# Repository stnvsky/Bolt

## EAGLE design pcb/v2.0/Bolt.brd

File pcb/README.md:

## PCB layout errata

### Integrated flash pins

GPIO pins from 6 to 11 are connected to the integrated SPI flash memory and are not safe to use. PCB versions 1.x suffer from the lack of prior knowledge of that, what caused the ESP32 to not be able to boot after the motors with hall sensors have been connected to the board. To avoid building second version of the PCB (what would cost lots of time and money, especially with the current lack of the electronic parts on the market), I've decided to resign from distance sensors to gain additional pins to be used for the hall sensors. Frankly, there weren't any possibility to use distance sensors in the first place, since ESP32 doesn't have enough pins to support three not-really-necessary sensors without GPIO's expander. 

Pins IMU_CLK and IMU_CS are connected consequentially to the pins SHD (hold) and SWP (write protect). As those pins are not directly responsible for carrying information in the flash SPI bus and are connected to the IMU input pins (so they are sending information to IMU, not receiving), the impact can be possibly not disastrous. I leaved those pins as they are, since it would be very difficult to workaround the direct connection with the IMU chip.

Other pins used for the communication with the integrated flash are prepared to be connected with the hall sensors. Since the hall sensors are sending information and the same pins are connected to the MISO, MOSI, CLK ans CS pins in integrated flash, the hall sensors interfere with the flash memory and can cause the ESP32 to brick and cannot boot no more. That's why the hall sensors will be connected to alternative pins:

| Signal   | Original pin | Alternative pin |
| -------- | ------------ | --------------- |
| HALL_1_A | 21 (GPIO 7)  | 4 (GPIO 36)     |
| HALL_2_A | 22 (GPIO 8)  | 7 (GPIO 35)     |
| HALL_1_B | 20 (GPIO 6)  | 10 (GPIO 25)    |
| HALL_2_B | 19 (GPIO 11) | 11 (GPIO 26)    |

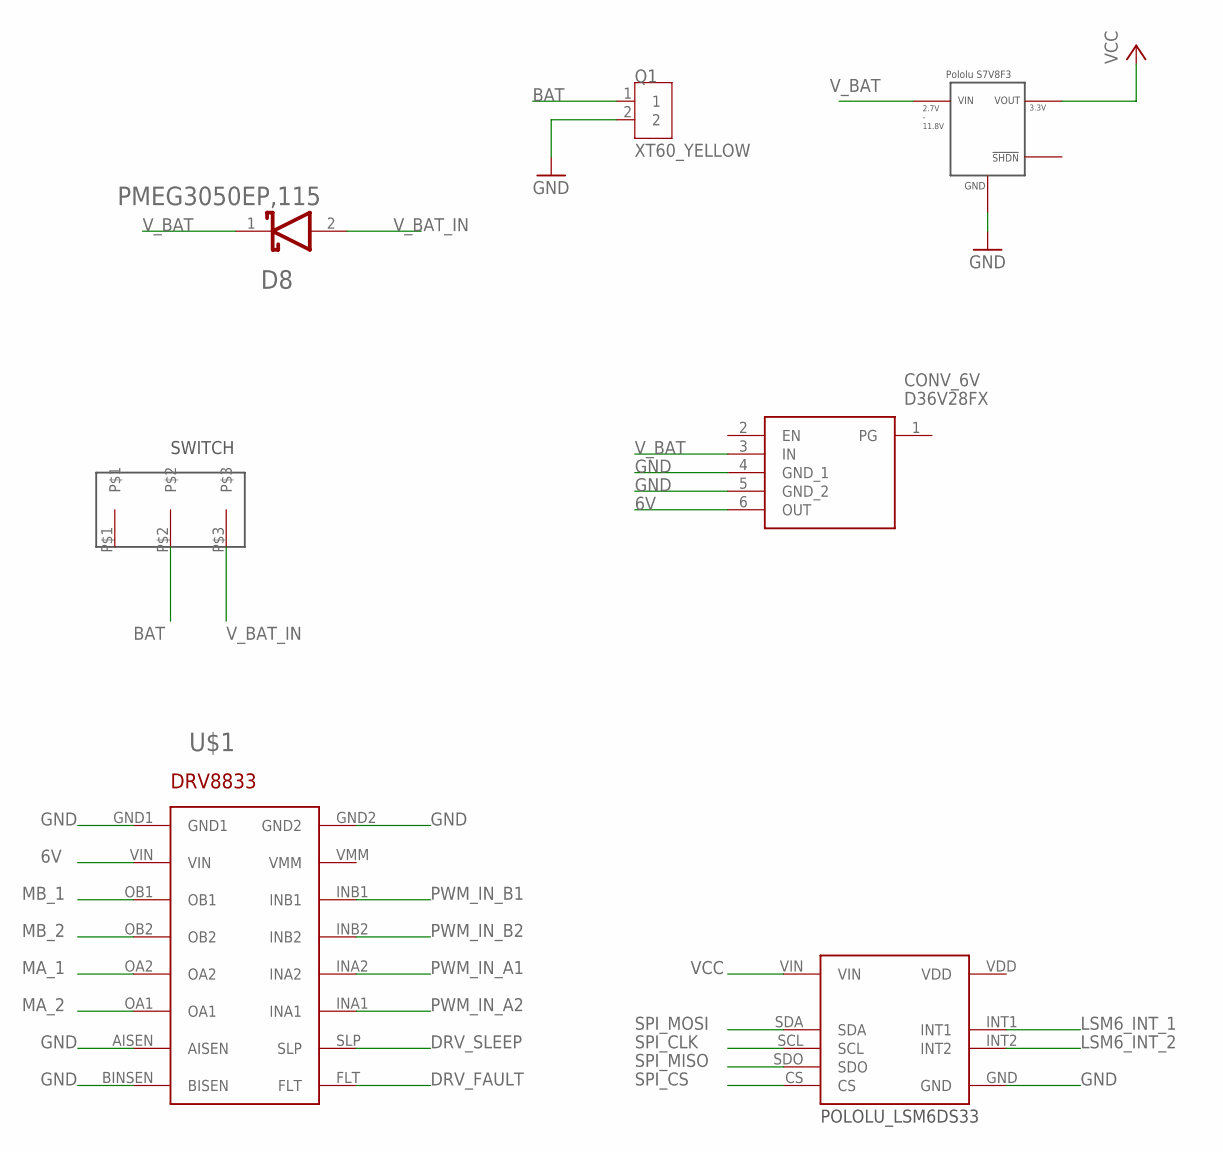
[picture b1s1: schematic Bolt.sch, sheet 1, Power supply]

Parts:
CONV_3V3: S7V8F3
CONV_6V: D36V28FX
D8: NEXPERIA_PMEG3050EP,115NEXPERIA_PMEG3050EP,115_0_0; NEXPERIA_PMEG3050EP,115_0
Q1: XT60_YELLOW; AMASS_XT60PB-M
U$1: POLOLU-DRV8833
U$2: POLOLU_LSM6DS33
U$3: SWITCH

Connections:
6V: CONV_6V.6 (OUT), U$1.VIN
BAT: Q1.1, U$3.P$2
DRV_FAULT: U$1.FLT; also elsewhere on the board
DRV_SLEEP: U$1.SLP; also elsewhere on the board
GND: CONV_3V3.GND, CONV_6V.4 (GND_1), CONV_6V.5 (GND_2), Q1.2, U$1.AISEN, U$1.BINSEN (BISEN), U$1.GND1, U$1.GND2, U$2.GND; also elsewhere on the board
LSM6_INT_1: U$2.INT1; also elsewhere on the board
LSM6_INT_2: U$2.INT2; also elsewhere on the board
MA_1: U$1.OA2; also elsewhere on the board
MA_2: U$1.OA1; also elsewhere on the board
MB_1: U$1.OB1; also elsewhere on the board
MB_2: U$1.OB2; also elsewhere on the board
PWM_IN_A1: U$1.INA2; also elsewhere on the board
PWM_IN_A2: U$1.INA1; also elsewhere on the board
PWM_IN_B1: U$1.INB1; also elsewhere on the board
PWM_IN_B2: U$1.INB2; also elsewhere on the board
SPI_CLK: U$2.SCL; also elsewhere on the board
SPI_CS: U$2.CS; also elsewhere on the board
SPI_MISO: U$2.SDO; also elsewhere on the board
SPI_MOSI: U$2.SDA; also elsewhere on the board
VCC: CONV_3V3.VOUT, U$2.VIN; also elsewhere on the board
V_BAT: CONV_3V3.VIN, CONV_6V.3 (IN), D8.1 (CATHODE)
V_BAT_IN: D8.2 (ANODE), U$3.P$3

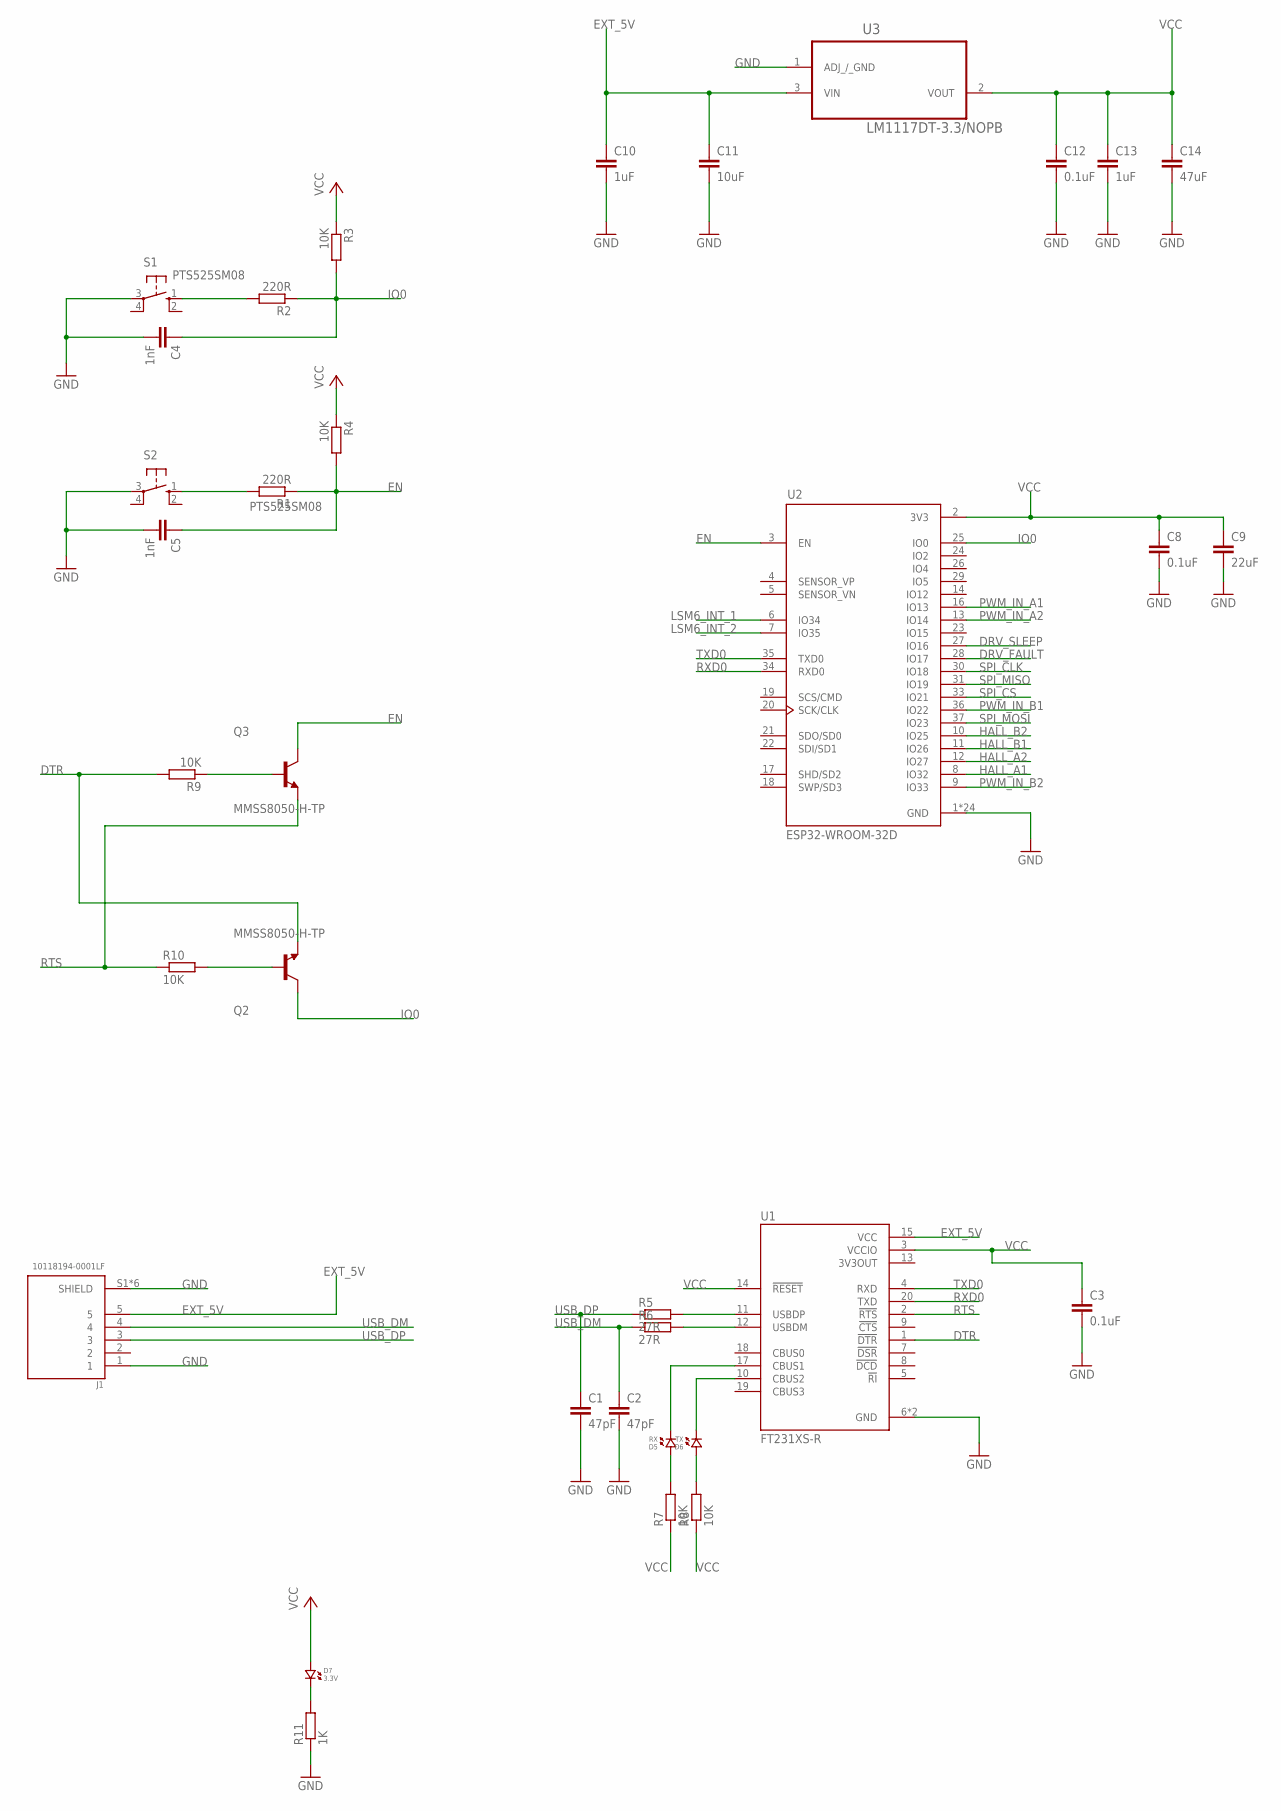
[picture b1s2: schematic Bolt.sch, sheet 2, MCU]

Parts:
C1, C2: 47pF; C0805K
C3, C8, C12: 0.1uF; C0805K
C4, C5: 1nF; C0805K
C9: 22uF; C0805K
C10, C13: 1uF; C0805K
C11: 10uF; C0805K
C14: 47uF; C0805K
D5: RX; 0805.LED
D6: TX; 0805.LED
D7: 3.3V; 0805.LED
J1: 10118194-0001LF; AMPHENOL_10118194-0001LF
Q2, Q3: MMSS8050-H-TP; TRANS_MMSS8050-H-TP
R1, R2: 220R; R0805
R3, R4, R7, R8, R9, R10: 10K; R0805
R5, R6: 27R; R0805
R11: 1K; R0805
S1, S2: PTS525SM08; SM08
U1: FT231XS-R; SOP63P599X175-20N
U2: ESP32-WROOM-32D; MODULE_ESP32-WROOM-32D
U3: LM1117DT-3.3/NOPB; TO228P970X238-3N

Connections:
3V3OUT: U1.13 (3V3OUT)
DRV_FAULT: U2.28 (IO17); also elsewhere on the board
DRV_SLEEP: U2.27 (IO16); also elsewhere on the board
DTR: Q2.2 (E), R9.2, U1.1 (!DTR)
EN: C5.1, Q3.3 (C), R1.1, R4.2, U2.3 (EN)
EXT_5V: C10.1, C11.1, J1.5, U1.15 (VCC), U3.3 (VIN)
GND: C1.2, C2.2, C3.2, C4.2, C5.2, C8.2, C9.2, C10.2, C11.2, C12.2, C13.2, C14.2, J1.1, J1.S1 (SHIELD), J1.S2 (SHIELD), J1.S3 (SHIELD), J1.S4 (SHIELD), J1.S5 (SHIELD), J1.S6 (SHIELD), R11.1, S1.3, S2.3, U1.6 (GND), U1.16 (GND), U2.1 (GND), U2.15 (GND), U2.38 (GND), U2.39_1 (GND), U2.39_2 (GND), U2.39_3 (GND), U2.39_4 (GND), U2.39_5 (GND), U2.39_6 (GND), U2.39_7 (GND), U2.39_8 (GND), U2.39_9 (GND), U2.39_10 (GND), U2.39_11 (GND), U2.39_12 (GND), U2.39_13 (GND), U2.39_14 (GND), U2.39_15 (GND), U2.39_16 (GND), U2.39_17 (GND), U2.39_18 (GND), U2.39_19 (GND), U2.39_20 (GND), U2.39_21 (GND), U3.1 (ADJ_/_GND); also elsewhere on the board
HALL_A1: U2.8 (IO32); also elsewhere on the board
HALL_A2: U2.12 (IO27); also elsewhere on the board
HALL_B1: U2.11 (IO26); also elsewhere on the board
HALL_B2: U2.10 (IO25); also elsewhere on the board
IO0: C4.1, Q2.3 (C), R2.1, R3.2, U2.25 (IO0)
LSM6_INT_1: U2.6 (IO34); also elsewhere on the board
LSM6_INT_2: U2.7 (IO35); also elsewhere on the board
unnamed: Q2.1 (B), R10.2
unnamed: D7.P$2 (2), R11.2
unnamed: D5.P$1 (1), R7.2
unnamed: R5.2, U1.11 (USBDP)
unnamed: R6.2, U1.12 (USBDM)
unnamed: R2.2, S1.1 (S)
unnamed: R1.2, S2.1 (S)
unnamed: Q3.1 (B), R9.1
unnamed: D5.P$2 (2), U1.17 (CBUS1)
unnamed: D6.P$2 (2), U1.10 (CBUS2)
unnamed: D6.P$1 (1), R8.2
PWM_IN_A1: U2.16 (IO13); also elsewhere on the board
PWM_IN_A2: U2.13 (IO14); also elsewhere on the board
PWM_IN_B1: U2.36 (IO22); also elsewhere on the board
PWM_IN_B2: U2.9 (IO33); also elsewhere on the board
RTS: Q3.2 (E), R10.1, U1.2 (!RTS)
RXD0: U1.20 (TXD), U2.34 (RXD0)
SPI_CLK: U2.30 (IO18); also elsewhere on the board
SPI_CS: U2.33 (IO21); also elsewhere on the board
SPI_MISO: U2.31 (IO19); also elsewhere on the board
SPI_MOSI: U2.37 (IO23); also elsewhere on the board
TXD0: U1.4 (RXD), U2.35 (TXD0)
USB_DM: C2.1, J1.4, R6.1
USB_DP: C1.1, J1.3, R5.1
VCC: C3.1, C8.1, C9.1, C12.1, C13.1, C14.1, D7.P$1 (1), R3.1, R4.1, R7.1, R8.1, U1.3 (VCCIO), U1.14 (!RESET), U2.2 (3V3), U3.2 (VOUT); also elsewhere on the board

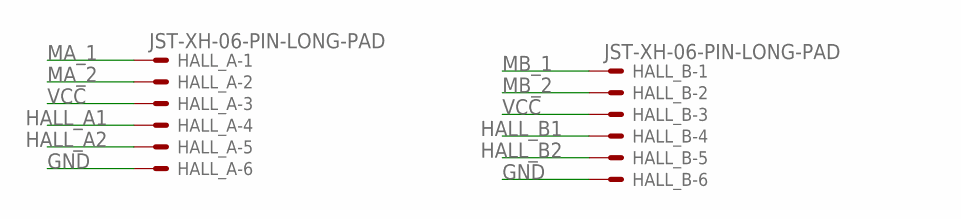
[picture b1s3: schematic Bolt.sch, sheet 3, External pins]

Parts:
HALL_A: JST-XH-06-PIN-LONG-PAD; JST-XH-06-PACKAGE-LONG-PAD
HALL_B: JST-XH-06-PIN-LONG-PAD; JST-XH-06-PACKAGE-LONG-PAD

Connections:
GND: HALL_A.6, HALL_B.6; also elsewhere on the board
HALL_A1: HALL_A.4; also elsewhere on the board
HALL_A2: HALL_A.5; also elsewhere on the board
HALL_B1: HALL_B.4; also elsewhere on the board
HALL_B2: HALL_B.5; also elsewhere on the board
MA_1: HALL_A.1; also elsewhere on the board
MA_2: HALL_A.2; also elsewhere on the board
MB_1: HALL_B.1; also elsewhere on the board
MB_2: HALL_B.2; also elsewhere on the board
VCC: HALL_A.3, HALL_B.3; also elsewhere on the board

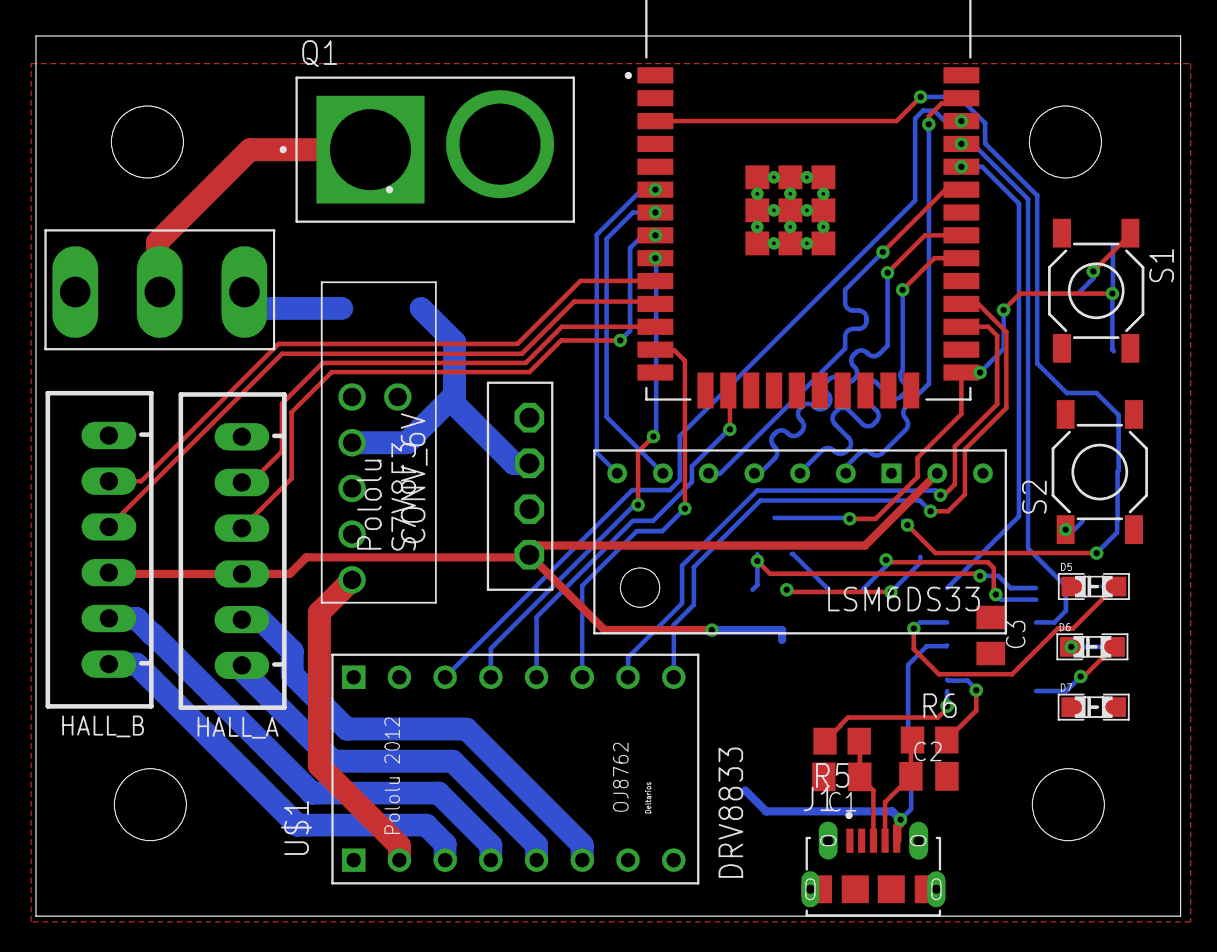
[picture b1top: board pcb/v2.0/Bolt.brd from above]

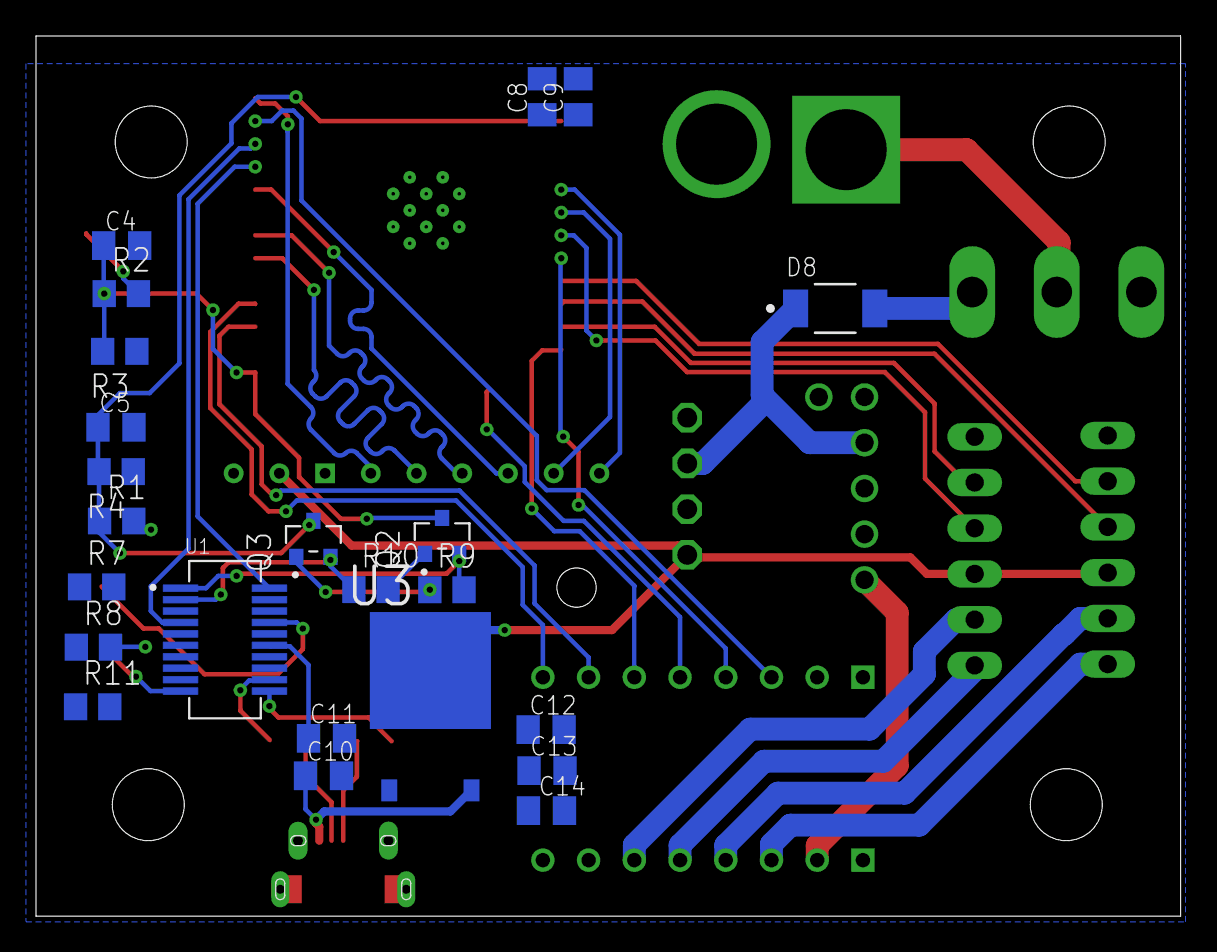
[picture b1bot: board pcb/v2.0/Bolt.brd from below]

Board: 2 copper layers, 63.6 x 48.9 mm, 43 parts (23 on the bottom side), 46 nets.

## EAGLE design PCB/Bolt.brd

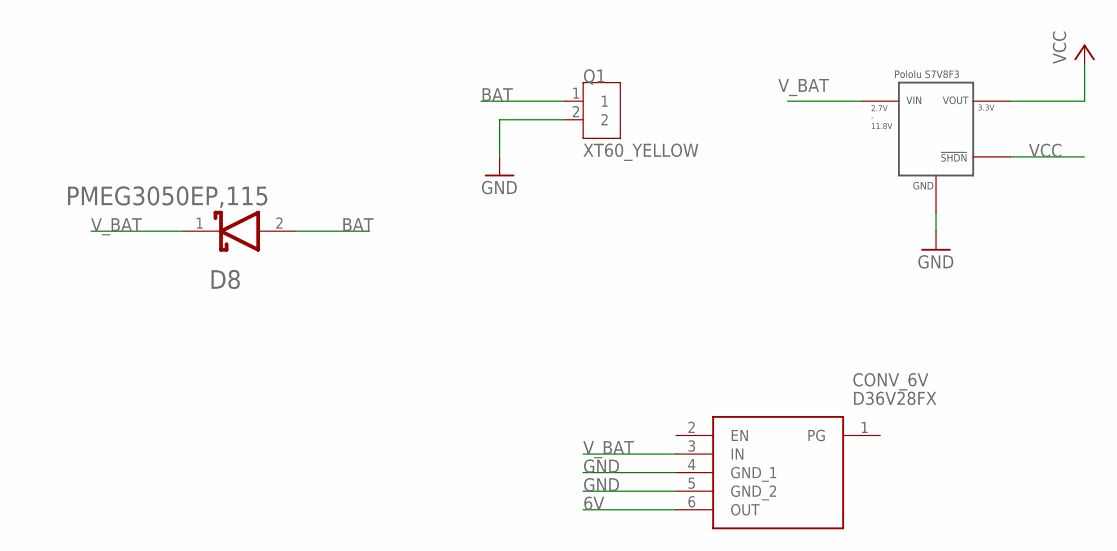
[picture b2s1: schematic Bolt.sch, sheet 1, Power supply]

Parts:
CONV_3V3: S7V8F3
CONV_6V: D36V28FX
D8: NEXPERIA_PMEG3050EP,115NEXPERIA_PMEG3050EP,115_0_0; NEXPERIA_PMEG3050EP,115_0
Q1: XT60_YELLOW; AMASS_XT60PB-M

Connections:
6V: CONV_6V.6 (OUT); also elsewhere on the board
BAT: D8.2 (ANODE), Q1.1
GND: CONV_3V3.GND, CONV_6V.4 (GND_1), CONV_6V.5 (GND_2), Q1.2; also elsewhere on the board
VCC: CONV_3V3.!SHDN, CONV_3V3.VOUT; also elsewhere on the board
V_BAT: CONV_3V3.VIN, CONV_6V.3 (IN), D8.1 (CATHODE)

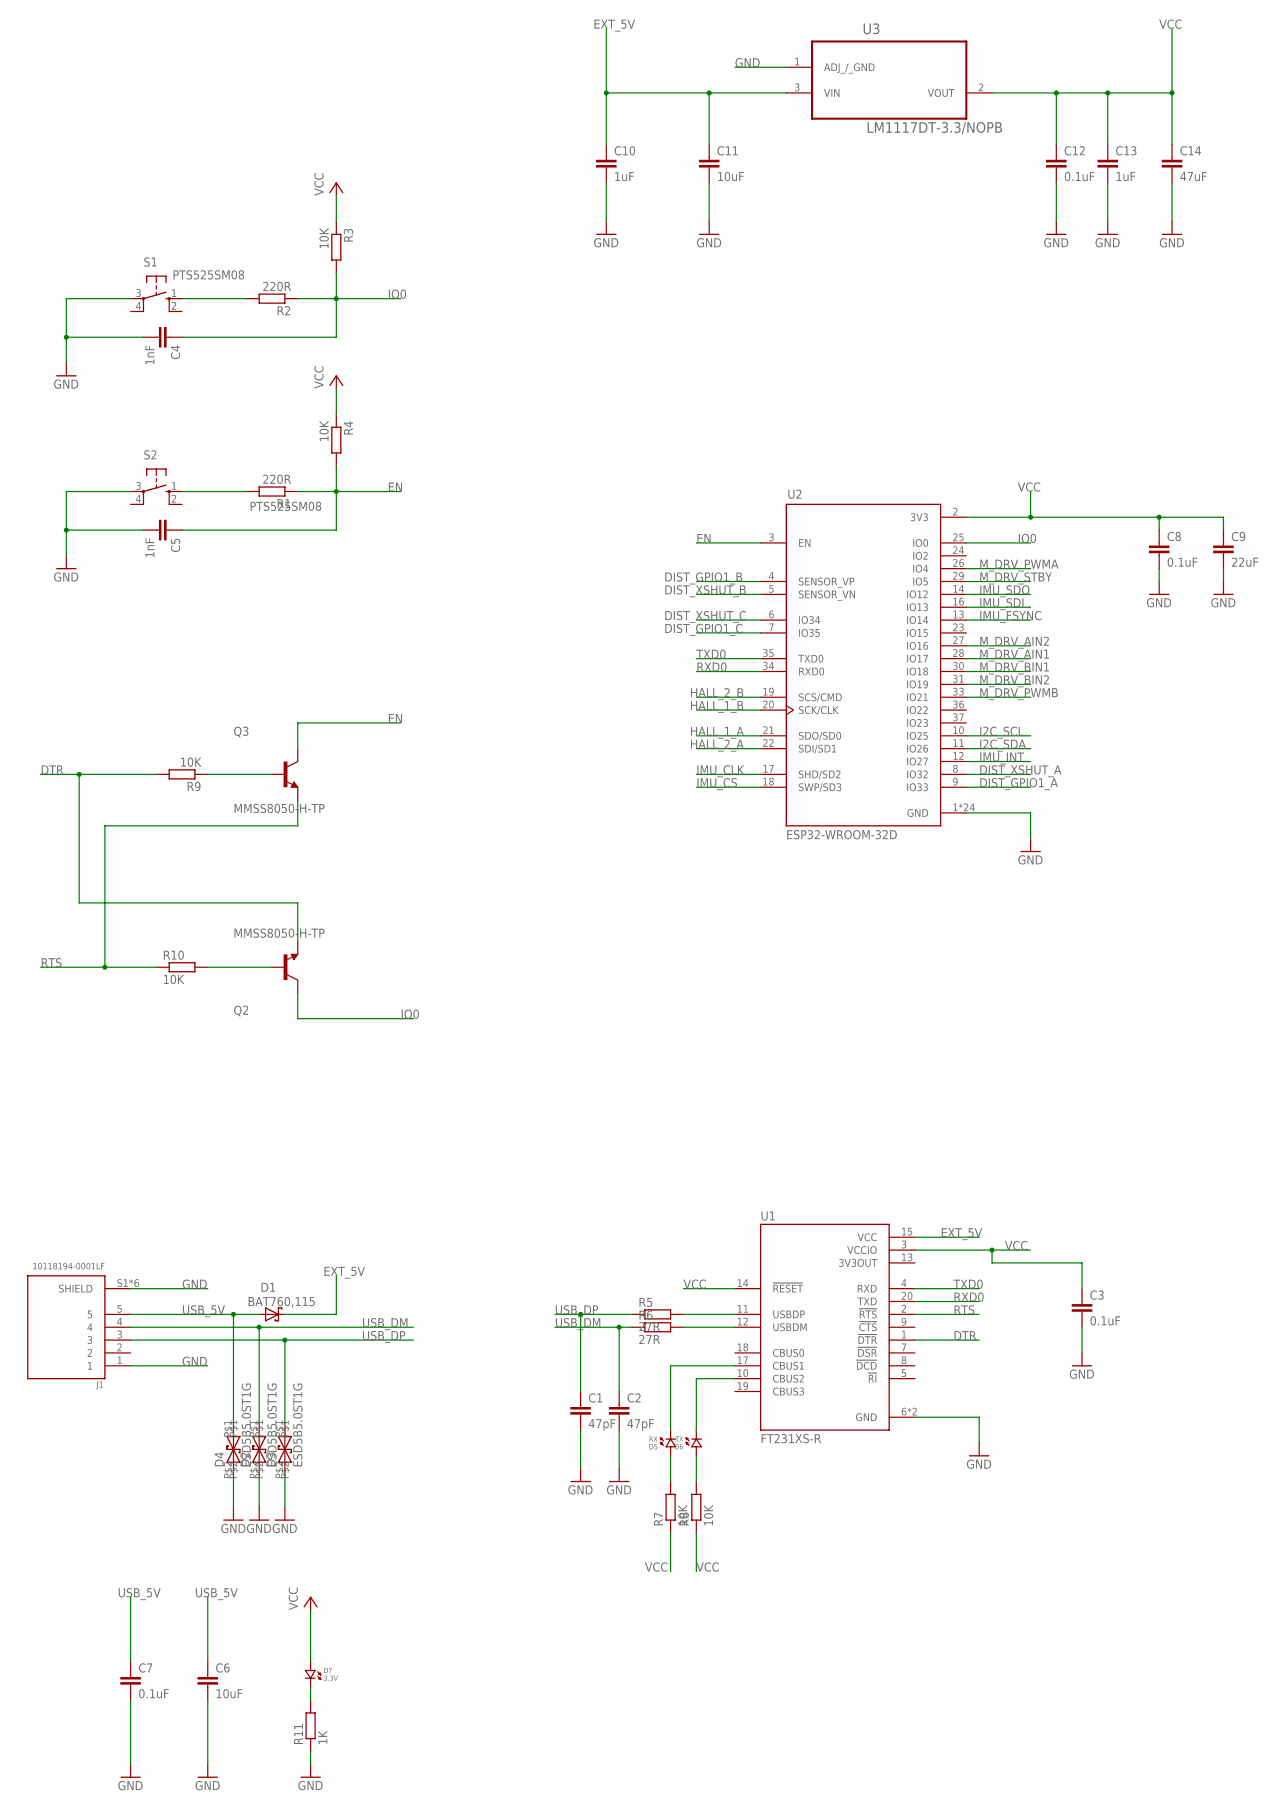
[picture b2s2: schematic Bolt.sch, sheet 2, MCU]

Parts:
C1, C2: 47pF; C0805K
C3, C7, C8, C12: 0.1uF; C0805K
C4, C5: 1nF; C0805K
C6, C11: 10uF; C0805K
C9: 22uF; C0805K
C10, C13: 1uF; C0805K
C14: 47uF; C0805K
D1: BAT760,115; SOD323(F)
D2, D3, D4: ESD5B5.0ST1G; SOD-523
D5: RX; 0805.LED
D6: TX; 0805.LED
D7: 3.3V; 0805.LED
J1: 10118194-0001LF; AMPHENOL_10118194-0001LF
Q2, Q3: MMSS8050-H-TP; TRANS_MMSS8050-H-TP
R1, R2: 220R; R0805
R3, R4, R7, R8, R9, R10: 10K; R0805
R5, R6: 27R; R0805
R11: 1K; R0805
S1, S2: PTS525SM08; SM08
U1: FT231XS-R; SOP63P599X175-20N
U2: ESP32-WROOM-32D; MODULE_ESP32-WROOM-32D
U3: LM1117DT-3.3/NOPB; TO228P970X238-3N

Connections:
3V3OUT: U1.13 (3V3OUT)
DIST_GPIO1_A: U2.9 (IO33); also elsewhere on the board
DIST_GPIO1_B: U2.4 (SENSOR_VP); also elsewhere on the board
DIST_GPIO1_C: U2.7 (IO35); also elsewhere on the board
DIST_XSHUT_A: U2.8 (IO32); also elsewhere on the board
DIST_XSHUT_B: U2.5 (SENSOR_VN); also elsewhere on the board
DIST_XSHUT_C: U2.6 (IO34); also elsewhere on the board
DTR: Q2.2 (E), R9.2, U1.1 (!DTR)
EN: C5.1, Q3.3 (C), R1.1, R4.2, U2.3 (EN)
EXT_5V: C10.1, C11.1, D1.1 (K), U1.15 (VCC), U3.3 (VIN)
GND: C1.2, C2.2, C3.2, C4.2, C5.2, C6.2, C7.2, C8.2, C9.2, C10.2, C11.2, C12.2, C13.2, C14.2, D2.P$2, D3.P$2, D4.P$2, J1.1, J1.S1 (SHIELD), J1.S2 (SHIELD), J1.S3 (SHIELD), J1.S4 (SHIELD), J1.S5 (SHIELD), J1.S6 (SHIELD), R11.1, S1.3, S2.3, U1.6 (GND), U1.16 (GND), U2.1 (GND), U2.15 (GND), U2.38 (GND), U2.39_1 (GND), U2.39_2 (GND), U2.39_3 (GND), U2.39_4 (GND), U2.39_5 (GND), U2.39_6 (GND), U2.39_7 (GND), U2.39_8 (GND), U2.39_9 (GND), U2.39_10 (GND), U2.39_11 (GND), U2.39_12 (GND), U2.39_13 (GND), U2.39_14 (GND), U2.39_15 (GND), U2.39_16 (GND), U2.39_17 (GND), U2.39_18 (GND), U2.39_19 (GND), U2.39_20 (GND), U2.39_21 (GND), U3.1 (ADJ_/_GND); also elsewhere on the board
HALL_1_A: U2.21 (SDO/SD0); also elsewhere on the board
HALL_1_B: U2.20 (SCK/CLK); also elsewhere on the board
HALL_2_A: U2.22 (SDI/SD1); also elsewhere on the board
HALL_2_B: U2.19 (SCS/CMD); also elsewhere on the board
I2C_SCL: U2.10 (IO25); also elsewhere on the board
I2C_SDA: U2.11 (IO26); also elsewhere on the board
IMU_CLK: U2.17 (SHD/SD2); also elsewhere on the board
IMU_CS: U2.18 (SWP/SD3); also elsewhere on the board
IMU_FSYNC: U2.13 (IO14); also elsewhere on the board
IMU_INT: U2.12 (IO27); also elsewhere on the board
IMU_SDI: U2.16 (IO13); also elsewhere on the board
IMU_SDO: U2.14 (IO12); also elsewhere on the board
IO0: C4.1, Q2.3 (C), R2.1, R3.2, U2.25 (IO0)
M_DRV_AIN1: U2.28 (IO17); also elsewhere on the board
M_DRV_AIN2: U2.27 (IO16); also elsewhere on the board
M_DRV_BIN1: U2.30 (IO18); also elsewhere on the board
M_DRV_BIN2: U2.31 (IO19); also elsewhere on the board
M_DRV_PWMA: U2.26 (IO4); also elsewhere on the board
M_DRV_PWMB: U2.33 (IO21); also elsewhere on the board
M_DRV_STBY: U2.29 (IO5); also elsewhere on the board
unnamed: Q2.1 (B), R10.2
unnamed: D7.P$2 (2), R11.2
unnamed: D5.P$1 (1), R7.2
unnamed: R5.2, U1.11 (USBDP)
unnamed: R6.2, U1.12 (USBDM)
unnamed: R2.2, S1.1 (S)
unnamed: R1.2, S2.1 (S)
unnamed: Q3.1 (B), R9.1
unnamed: D5.P$2 (2), U1.17 (CBUS1)
unnamed: D6.P$2 (2), U1.10 (CBUS2)
unnamed: D6.P$1 (1), R8.2
RTS: Q3.2 (E), R10.1, U1.2 (!RTS)
RXD0: U1.20 (TXD), U2.34 (RXD0)
TXD0: U1.4 (RXD), U2.35 (TXD0)
USB_5V: C6.1, C7.1, D1.2 (A), D4.P$1, J1.5
USB_DM: C2.1, D2.P$1, J1.4, R6.1
USB_DP: C1.1, D3.P$1, J1.3, R5.1
VCC: C3.1, C8.1, C9.1, C12.1, C13.1, C14.1, D7.P$1 (1), R3.1, R4.1, R7.1, R8.1, U1.3 (VCCIO), U1.14 (!RESET), U2.2 (3V3), U3.2 (VOUT); also elsewhere on the board

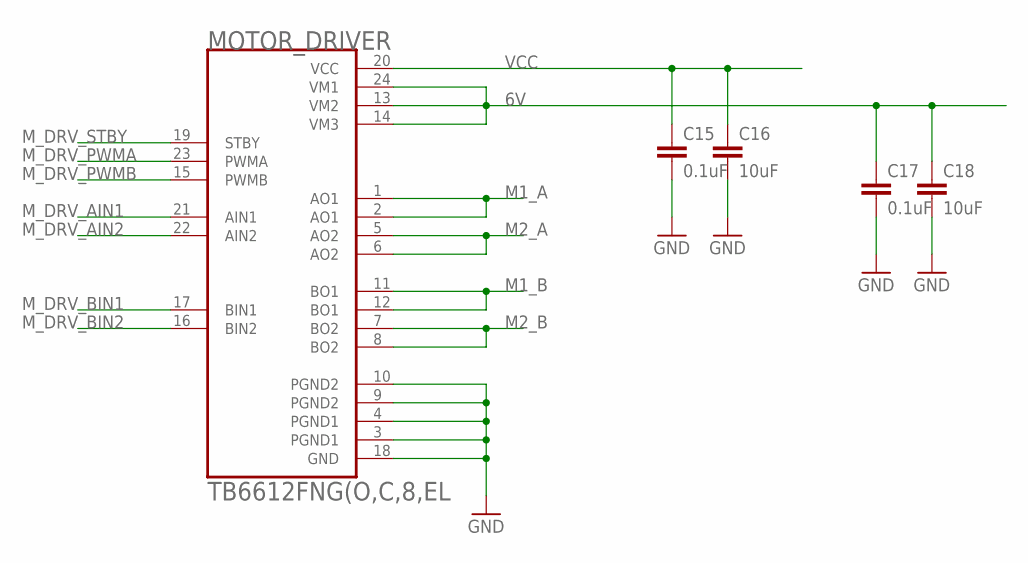
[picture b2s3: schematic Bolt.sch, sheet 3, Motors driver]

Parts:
C15, C17: 0.1uF; C0805K
C16, C18: 10uF; C0805K
MOTOR_DRIVER: TB6612FNG(O,C,8,EL; SOP65P760X160-24N

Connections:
6V: C17.1, C18.1, MOTOR_DRIVER.13 (VM2), MOTOR_DRIVER.14 (VM3), MOTOR_DRIVER.24 (VM1); also elsewhere on the board
GND: C15.2, C16.2, C17.2, C18.2, MOTOR_DRIVER.3 (PGND1), MOTOR_DRIVER.4 (PGND1), MOTOR_DRIVER.9 (PGND2), MOTOR_DRIVER.10 (PGND2), MOTOR_DRIVER.18 (GND); also elsewhere on the board
M1_A: MOTOR_DRIVER.1 (AO1), MOTOR_DRIVER.2 (AO1); also elsewhere on the board
M1_B: MOTOR_DRIVER.11 (BO1), MOTOR_DRIVER.12 (BO1); also elsewhere on the board
M2_A: MOTOR_DRIVER.5 (AO2), MOTOR_DRIVER.6 (AO2); also elsewhere on the board
M2_B: MOTOR_DRIVER.7 (BO2), MOTOR_DRIVER.8 (BO2); also elsewhere on the board
M_DRV_AIN1: MOTOR_DRIVER.21 (AIN1); also elsewhere on the board
M_DRV_AIN2: MOTOR_DRIVER.22 (AIN2); also elsewhere on the board
M_DRV_BIN1: MOTOR_DRIVER.17 (BIN1); also elsewhere on the board
M_DRV_BIN2: MOTOR_DRIVER.16 (BIN2); also elsewhere on the board
M_DRV_PWMA: MOTOR_DRIVER.23 (PWMA); also elsewhere on the board
M_DRV_PWMB: MOTOR_DRIVER.15 (PWMB); also elsewhere on the board
M_DRV_STBY: MOTOR_DRIVER.19 (STBY); also elsewhere on the board
VCC: C15.1, C16.1, MOTOR_DRIVER.20 (VCC); also elsewhere on the board

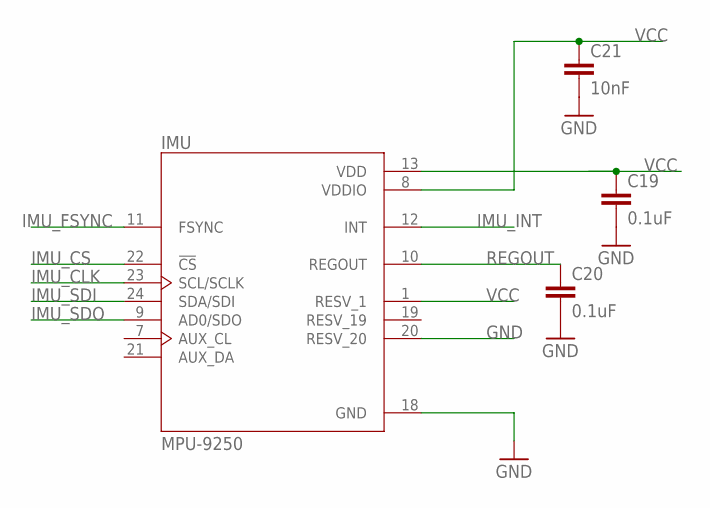
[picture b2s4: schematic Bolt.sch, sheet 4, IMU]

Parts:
C19, C20: 0.1uF; C0805K
C21: 10nF; C0805K
IMU: MPU-9250; QFN40P300X300X105-24N

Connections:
GND: C19.2, C20.2, C21.2, IMU.18 (GND), IMU.20 (RESV_20); also elsewhere on the board
IMU_CLK: IMU.23 (SCL/SCLK); also elsewhere on the board
IMU_CS: IMU.22 (!CS); also elsewhere on the board
IMU_FSYNC: IMU.11 (FSYNC); also elsewhere on the board
IMU_INT: IMU.12 (INT); also elsewhere on the board
IMU_SDI: IMU.24 (SDA/SDI); also elsewhere on the board
IMU_SDO: IMU.9 (AD0/SDO); also elsewhere on the board
REGOUT: C20.1, IMU.10 (REGOUT)
VCC: C19.1, C21.1, IMU.1 (RESV_1), IMU.8 (VDDIO), IMU.13 (VDD); also elsewhere on the board

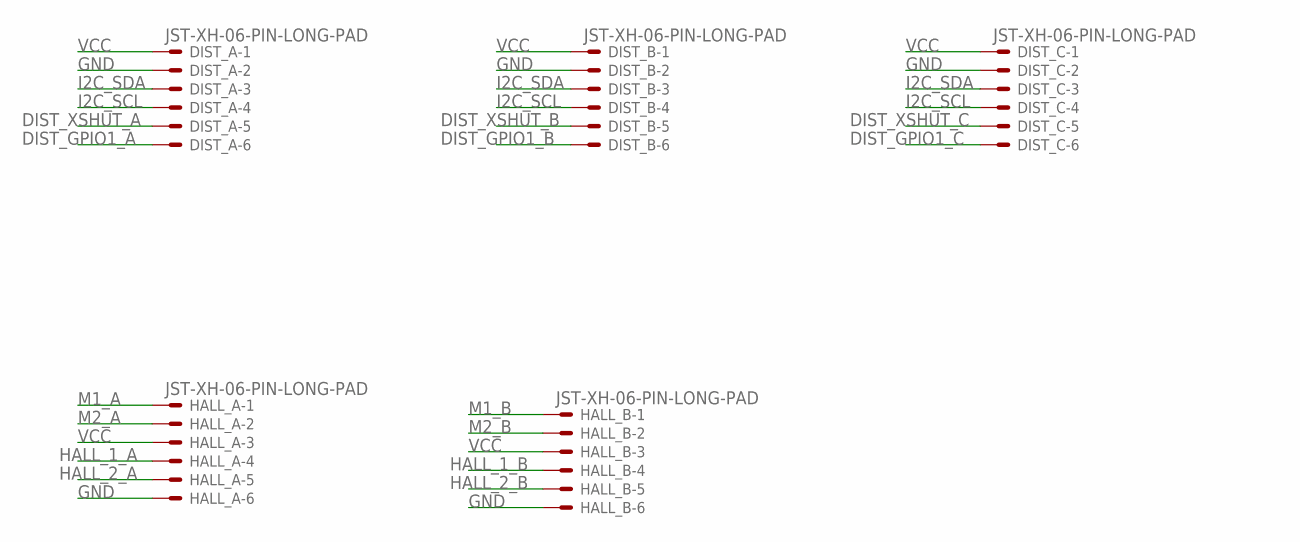
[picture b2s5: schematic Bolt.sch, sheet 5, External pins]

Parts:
DIST_A: JST-XH-06-PIN-LONG-PAD; JST-XH-06-PACKAGE-LONG-PAD
DIST_B: JST-XH-06-PIN-LONG-PAD; JST-XH-06-PACKAGE-LONG-PAD
DIST_C: JST-XH-06-PIN-LONG-PAD; JST-XH-06-PACKAGE-LONG-PAD
HALL_A: JST-XH-06-PIN-LONG-PAD; JST-XH-06-PACKAGE-LONG-PAD
HALL_B: JST-XH-06-PIN-LONG-PAD; JST-XH-06-PACKAGE-LONG-PAD

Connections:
DIST_GPIO1_A: DIST_A.6; also elsewhere on the board
DIST_GPIO1_B: DIST_B.6; also elsewhere on the board
DIST_GPIO1_C: DIST_C.6; also elsewhere on the board
DIST_XSHUT_A: DIST_A.5; also elsewhere on the board
DIST_XSHUT_B: DIST_B.5; also elsewhere on the board
DIST_XSHUT_C: DIST_C.5; also elsewhere on the board
GND: DIST_A.2, DIST_B.2, DIST_C.2, HALL_A.6, HALL_B.6; also elsewhere on the board
HALL_1_A: HALL_A.4; also elsewhere on the board
HALL_1_B: HALL_B.4; also elsewhere on the board
HALL_2_A: HALL_A.5; also elsewhere on the board
HALL_2_B: HALL_B.5; also elsewhere on the board
I2C_SCL: DIST_A.4, DIST_B.4, DIST_C.4; also elsewhere on the board
I2C_SDA: DIST_A.3, DIST_B.3, DIST_C.3; also elsewhere on the board
M1_A: HALL_A.1; also elsewhere on the board
M1_B: HALL_B.1; also elsewhere on the board
M2_A: HALL_A.2; also elsewhere on the board
M2_B: HALL_B.2; also elsewhere on the board
VCC: DIST_A.1, DIST_B.1, DIST_C.1, HALL_A.3, HALL_B.3; also elsewhere on the board

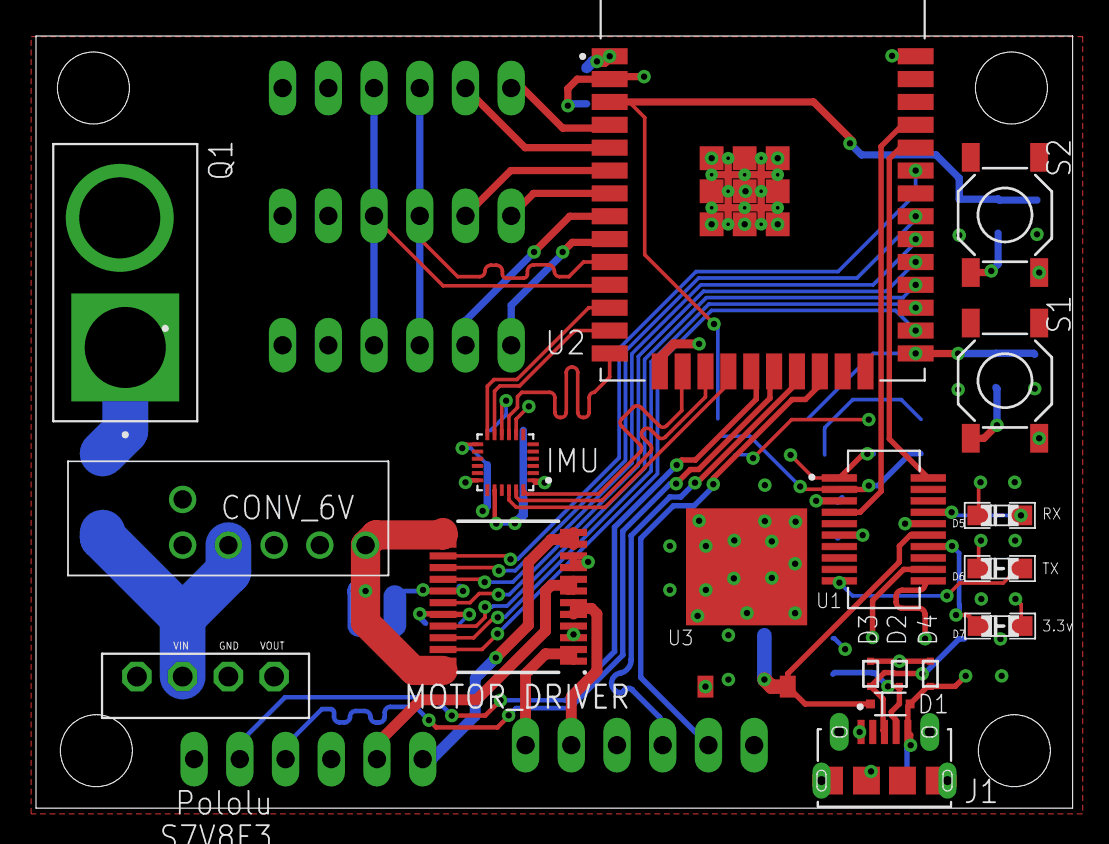
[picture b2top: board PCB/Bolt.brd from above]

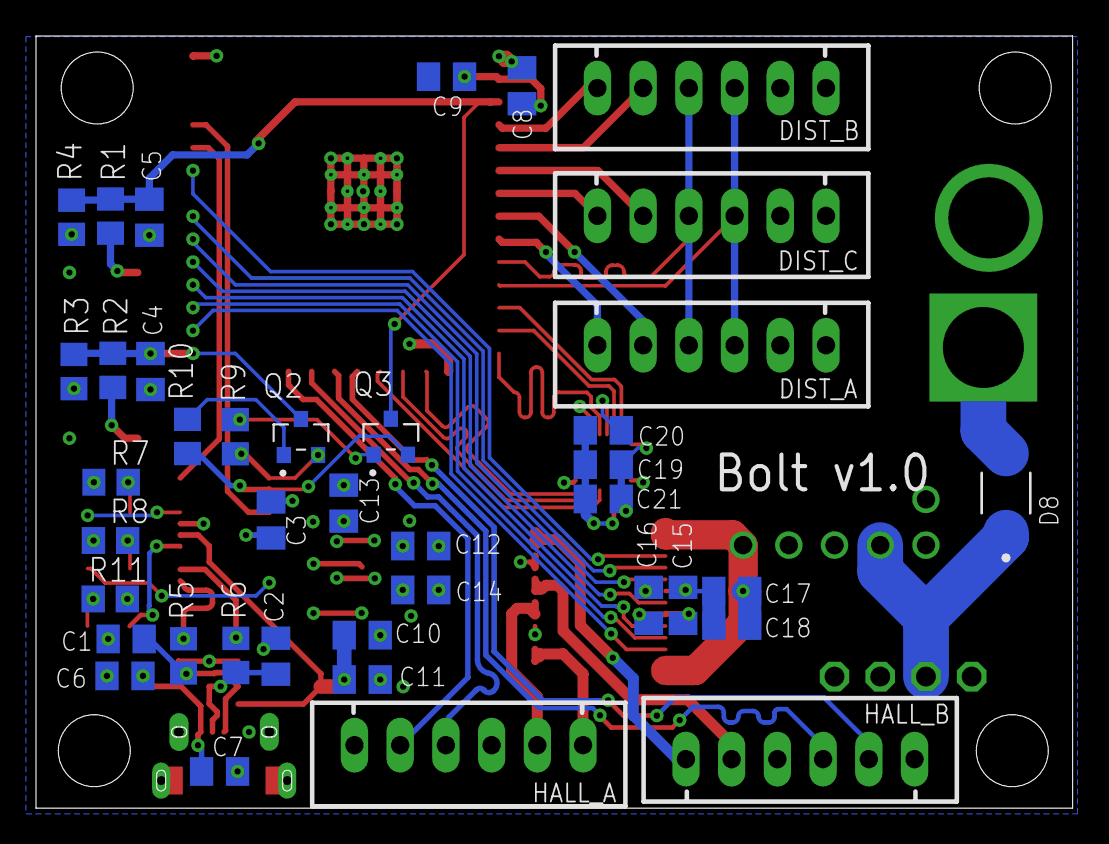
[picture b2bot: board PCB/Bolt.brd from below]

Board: 4 copper layers, 57.6 x 42.9 mm, 58 parts (40 on the bottom side), 56 nets.

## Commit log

2021-01-16 Choose of the pcb elements
2021-01-17 Added UART-USB converter
2021-01-18 Schematic completed
2021-01-19 Board - work in progress
2021-01-20 Board completed
2021-02-10 Bolt v1.0
2021-03-30 added initial code with some components, project refactoring
2021-04-18 Distance sensors - writing own library
2021-04-20 Distance sensors work
2021-04-26 refactor
2022-03-18 Fixed XSHUT routes on PCB resulting in Bolt v1.1
2022-06-07 Starting to work on the encoders
2022-06-08 Migrated to esp-idf v5.0, removed 'encoder' component
2022-06-09 Added first schetch for the vehicle model
2022-06-09 First prototype for the motors and dummy support for PCB
2022-06-09 Divided model to two bodies
2022-06-10 Fixed problems with the project, added fillets and holes in the motors base body
2022-06-10 Bottom part candidate
2022-06-10 Added PCB support model
2022-06-10 model candidate
2022-06-10 Vehicle structure model v1.0
2022-06-13 Added stl model of the whole vehicle construction
2022-06-14 Motors driver refactoring
2022-06-14 Working on the second version of the PCB
2022-06-15 Bolt v2.0 - before routing
2022-06-16 Routes except VCC
2022-06-17 Fixed removing v1.0 from the repository
2022-08-29 PCB v1.1 layout errata
2022-08-29 refactored directory pcb
2022-08-29 moved .gitignore to pcb subdirectories
2022-08-30 Refactoring, working example with acceleration
2022-08-30 pcb/v1.1./README.md update
2022-08-30 Implemented method for setting motors speed in range [-100, 100]
2022-08-30 Added example GPIO interrupt handlers
2022-09-02 Reading velocity and direction from hall sensors
2022-09-03 Get motors speed in [m/s]
2022-09-03 Updated the MPU library with DMP support
2022-09-03 Quaternions support
2022-09-03 Revert "Quaternions support"
    This reverts commit 9693c5bfa1dd5aa4b6852ace6723c310ea848c24.
2022-09-03 Implemented roll measurement using only accelerometer
2022-09-04 Control prototype
2022-09-04 Migrated to the newest version of esp-idf environment
2022-09-04 Added matlab/simulink model
2022-09-05 Added console command line for changing controllers parameters
2022-09-05 Added example data for the Kalman filter implementation
2022-09-06 Implemented Kalman filter in matlab
2022-09-06 Implemented kalman filter, but roll data is still drifting
2022-09-07 Fixed kalman filter
2022-09-07 Refactored ange data format from int to float
2022-09-07 Added example UDP client
2022-09-07 Added config with wifi credentials
2022-09-07 Changed wifi_config.h name to wifi_config.h.in
2022-09-08 Sending roll data through the UDP socket
2022-09-08 Added test tool for drawing roll angle in time using UDP sockets
2022-09-09 Changing Kp1 using UDP server
2022-09-10 Refined control task, added udp client task alongside with the udp server task
